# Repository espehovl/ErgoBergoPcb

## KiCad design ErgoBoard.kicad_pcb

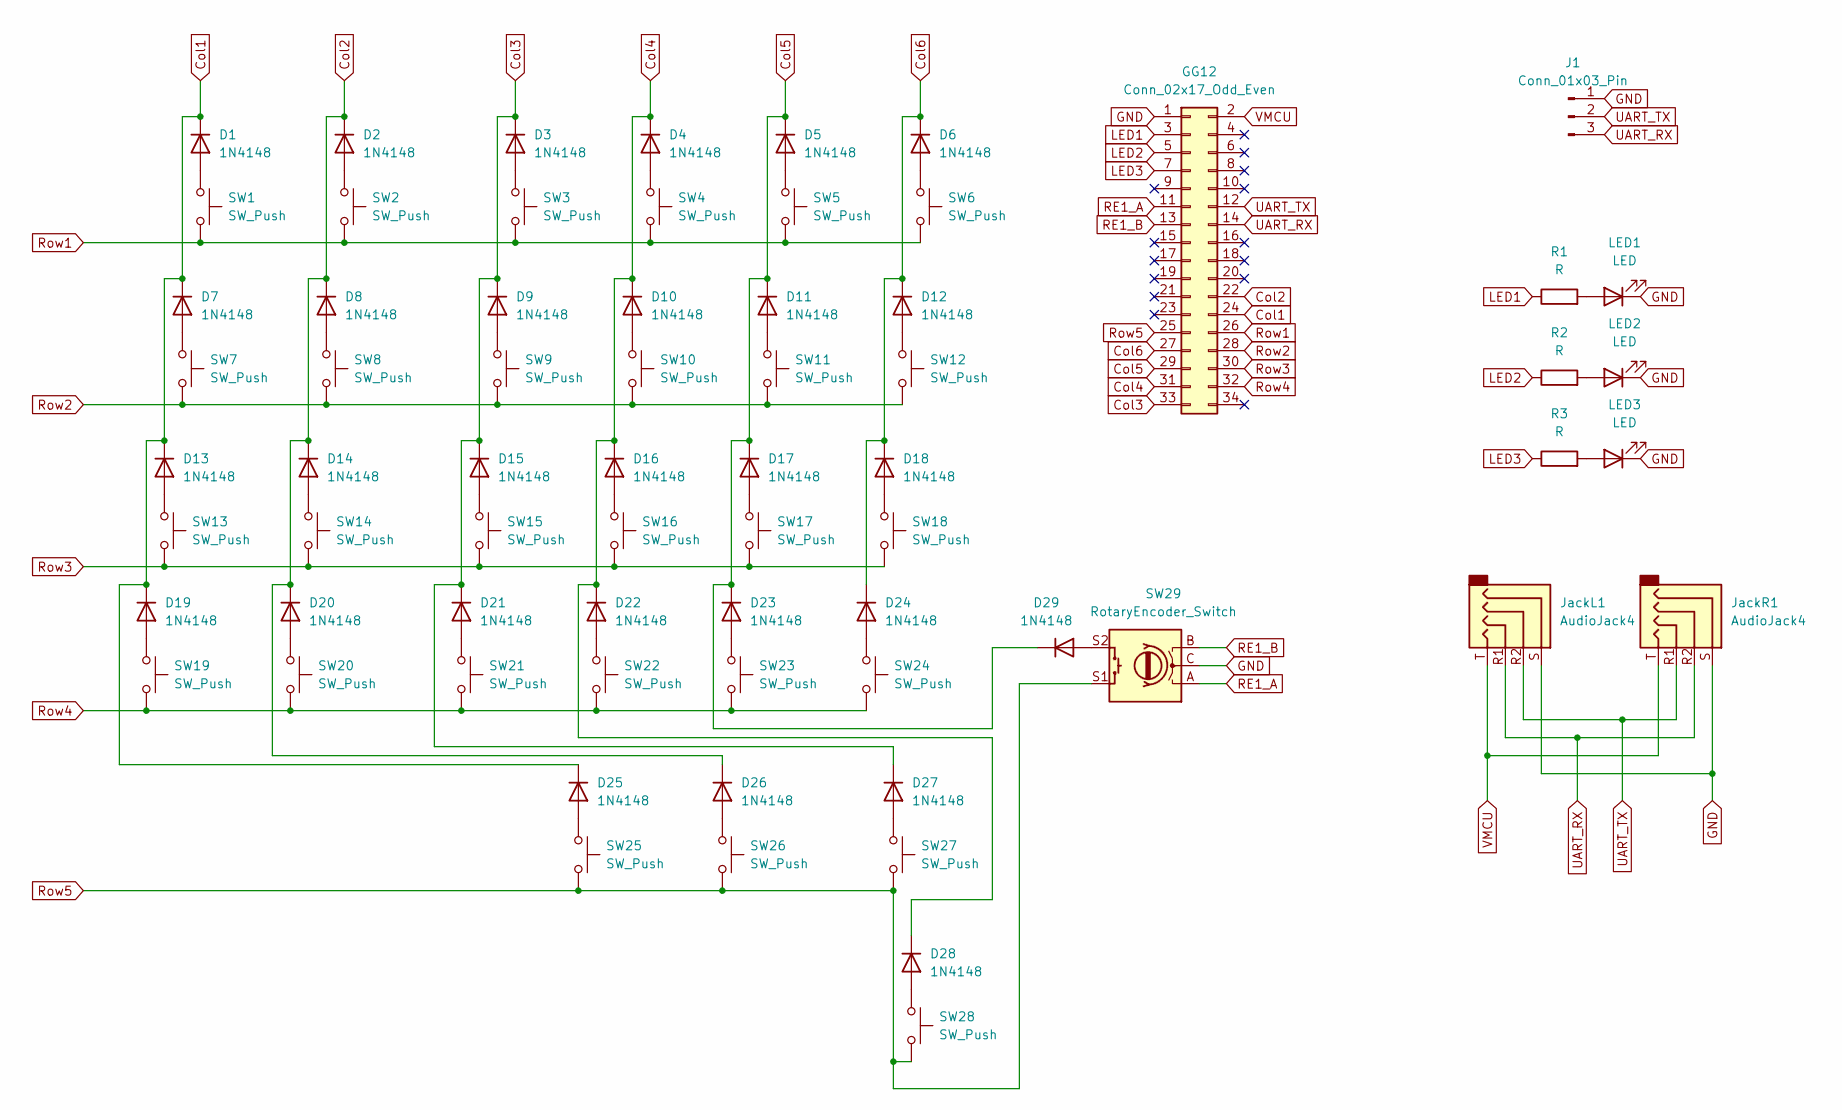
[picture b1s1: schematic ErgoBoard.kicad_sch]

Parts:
D1, D2, D3, D4, D5, D6, D7, D8, D9, D10, D11, D12, D13, D14, D15, D16, D17, D18, D19, D20, D21, D22, D23, D24, D25, D26, D27, D28, D29: 1N4148; D_DO-35_SOD27_P7.62mm_Horizontal
GG12: Conn_02x17_Odd_Even; GG12 SMD
J1: Conn_01x03_Pin; PinHeader_1x03_P2.54mm_Vertical
JackL1: AudioJack4; Jack_3.5mm_PJ320D_Horizontal
JackR1: AudioJack4; Jack_3.5mm_PJ320D_Horizontal
LED1, LED2, LED3: LED; LED_D5.0mm
R1, R2, R3: R; R_Axial_DIN0207_L6.3mm_D2.5mm_P10.16mm_Horizontal
SW1, SW2, SW3, SW4, SW5, SW6, SW7, SW8, SW9, SW10, SW11, SW12, SW13, SW14, SW15, SW16, SW17, SW18, SW19, SW20, SW21, SW22, SW23, SW24, SW25, SW26, SW27, SW28: SW_Push; Kailh_socket_PG1350_reversible
SW29: RotaryEncoder_Switch; RotaryEncoder_Alps_EC11E-Switch_Vertical_H20mm

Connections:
Col1: D1.1 (K), D7.1 (K), D13.1 (K), D19.1 (K), D25.1 (K), GG12.24
Col2: D2.1 (K), D8.1 (K), D14.1 (K), D20.1 (K), D26.1 (K), GG12.22
Col3: D3.1 (K), D9.1 (K), D15.1 (K), D21.1 (K), D27.1 (K), GG12.33
Col4: D4.1 (K), D10.1 (K), D16.1 (K), D22.1 (K), D28.1 (K), GG12.31
Col5: D5.1 (K), D11.1 (K), D17.1 (K), D23.1 (K), D29.1 (K), GG12.29
Col6: D6.1 (K), D12.1 (K), D18.1 (K), D24.1 (K), GG12.27
GND: GG12.1 (GND), J1.1, JackL1.S, JackR1.S, LED1.1 (K), LED2.1 (K), LED3.1 (K), SW29.C; also elsewhere on the board
LED1: GG12.3, R1.1
LED2: GG12.5, R2.1
LED3: GG12.7, R3.1
unnamed: D1.2 (A), SW1.1
unnamed: D2.2 (A), SW2.1
unnamed: D3.2 (A), SW3.1
unnamed: D4.2 (A), SW4.1
unnamed: D5.2 (A), SW5.1
unnamed: D6.2 (A), SW6.1
unnamed: D7.2 (A), SW7.1
unnamed: D8.2 (A), SW8.1
unnamed: D9.2 (A), SW9.1
unnamed: D10.2 (A), SW10.1
unnamed: D11.2 (A), SW11.1
unnamed: D12.2 (A), SW12.1
unnamed: D13.2 (A), SW13.1
unnamed: D14.2 (A), SW14.1
unnamed: D15.2 (A), SW15.1
unnamed: D16.2 (A), SW16.1
unnamed: D17.2 (A), SW17.1
unnamed: D18.2 (A), SW18.1
unnamed: D19.2 (A), SW19.1
unnamed: D20.2 (A), SW20.1
unnamed: D21.2 (A), SW21.1
unnamed: D22.2 (A), SW22.1
unnamed: D23.2 (A), SW23.1
unnamed: D24.2 (A), SW24.1
unnamed: D25.2 (A), SW25.1
unnamed: D26.2 (A), SW26.1
unnamed: D27.2 (A), SW27.1
unnamed: D28.2 (A), SW28.1
unnamed: D29.2 (A), SW29.S2
unnamed: LED1.2 (A), R1.2
unnamed: LED2.2 (A), R2.2
unnamed: LED3.2 (A), R3.2
RE1_A: GG12.11, SW29.A
RE1_B: GG12.13, SW29.B
Row1: GG12.26, SW1.2, SW2.2, SW3.2, SW4.2, SW5.2, SW6.2
Row2: GG12.28, SW7.2, SW8.2, SW9.2, SW10.2, SW11.2, SW12.2
Row3: GG12.30, SW13.2, SW14.2, SW15.2, SW16.2, SW17.2, SW18.2
Row4: GG12.32, SW19.2, SW20.2, SW21.2, SW22.2, SW23.2, SW24.2
Row5: GG12.25, SW25.2, SW26.2, SW27.2, SW28.2, SW29.S1
UART_RX: GG12.14, J1.3, JackL1.R1, JackR1.R2; also elsewhere on the board
UART_TX: GG12.12, J1.2, JackL1.R2, JackR1.R1; also elsewhere on the board
VMCU: GG12.2, JackL1.T, JackR1.T; also elsewhere on the board

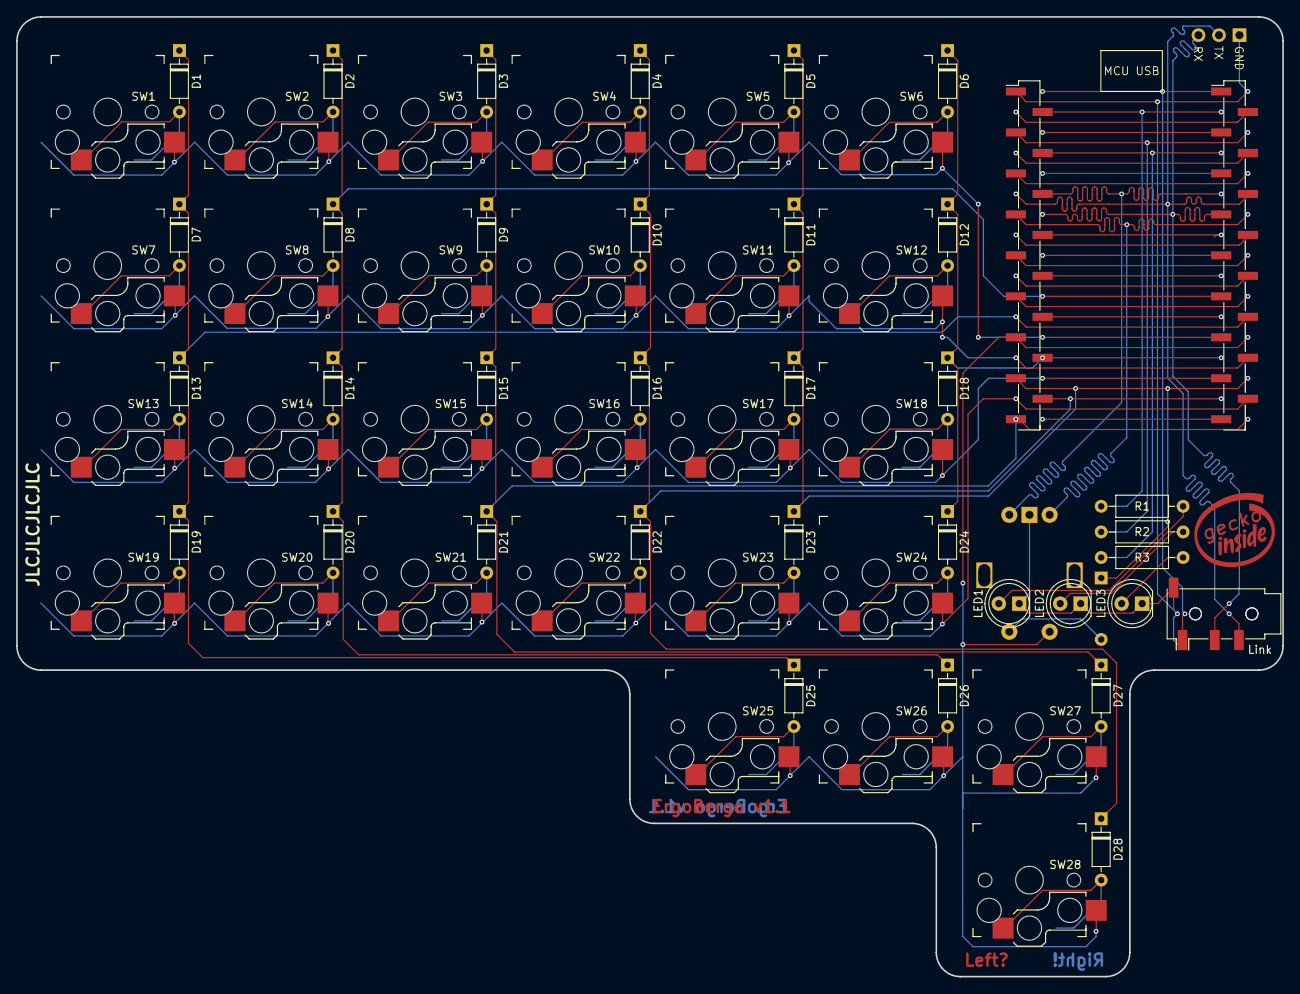
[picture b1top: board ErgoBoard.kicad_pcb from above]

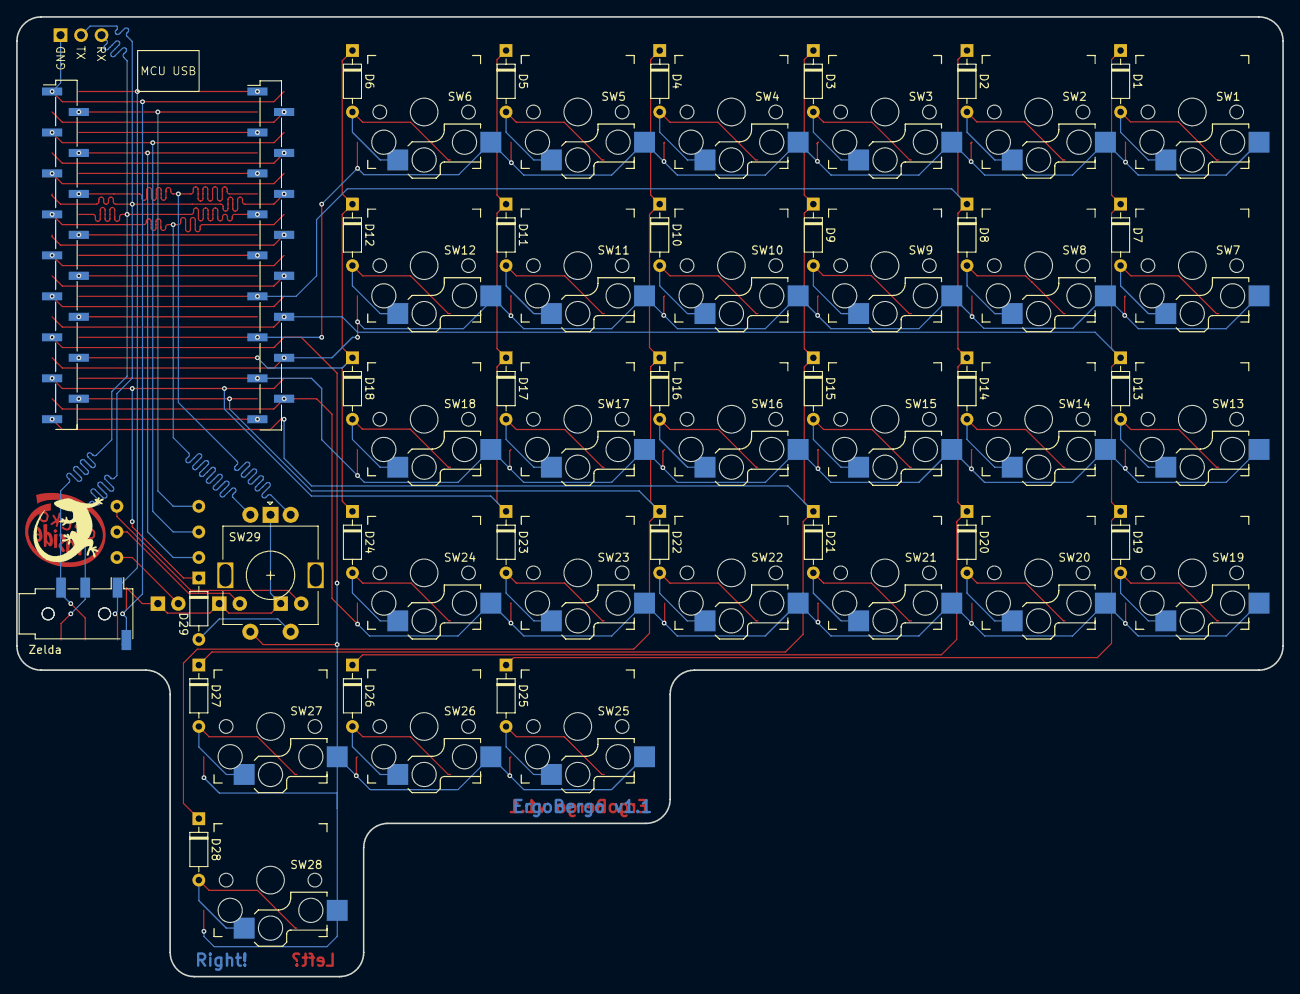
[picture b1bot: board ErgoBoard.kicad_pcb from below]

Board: 2 copper layers, 157.0 x 119.0 mm, 68 parts (3 on the bottom side), 52 nets.

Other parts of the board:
Link: AudioJack4; Jack_3.5mm_PJ320D_Horizontal
Zelda: AudioJack4; Jack_3.5mm_PJ320D_Horizontal

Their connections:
GND: Link.S, Zelda.S; also elsewhere on the board
UART_RX: Link.R1, Zelda.R2; also elsewhere on the board
UART_TX: Link.R2, Zelda.R1; also elsewhere on the board
VMCU: Link.T, Zelda.T; also elsewhere on the board

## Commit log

2024-12-19 Initial commit v1.1
2024-12-19 Add .gitignore
2025-01-05 Add UART debug test points
2025-01-12 Update schematic pdf
2025-02-24 Updated step file
